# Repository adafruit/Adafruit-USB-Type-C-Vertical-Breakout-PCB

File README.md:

## Adafruit USB Type C Vertical Breakout - Downstream Connection PCB

<a href="http://www.adafruit.com/products/5993"><br/>
Click here to purchase one from the Adafruit shop</a>

PCB files for the Adafruit USB Type C Vertical Breakout - Downstream Connection. 

Format is EagleCAD schematic and board layout
* https://www.adafruit.com/product/5993

### Description

Throw out all those Mini and Micro B USB cables you have in a plastic bin; the next generation of USB connectors is here with USB C! You will start to see these connectors pop up on all sorts of devices as the industry moves from micro B or lightening to the new standard. Well, at least until the next standard comes out.

This is the vertical version. We also carry a classic 'horizontal' USB-C breakout here.

USB C features a symmetric/reversible connector, more data pins, and higher current output capability. But, for most developers, the pin usage you know and love from older USB will work just fine. This breakout gives you all the basics you need and a resistor configuration that mimics classic USB 2.0 for a downstream connection

The two 5.1K resistors on the CC pins indicate to the upstream port to provide 5V and up to 1.5A (whether the upstream can supply that much current depends on what you're connecting to.

For most usages, you can connect VBUS to your 5V input, GND to ground, and D+ and D- as you expect. You can monitor the CC and SBU pins to determine cable polarity or send side-band data. Or leave them disconnected.

Since this connector is vertical, we give you two identical breakout strips so it will stand flat on a breadboard, plus four mounting holes in case you want to attach this to an enclosure.

[For more details, we like this Introduction to USB C app note.](http://ww1.microchip.com/downloads/en/appnotes/00001953a.pdf)

### License

Adafruit invests time and resources providing this open source design, please support Adafruit and open-source hardware by purchasing products from [Adafruit](https://www.adafruit.com)!

Designed by Limor Fried/Ladyada for Adafruit Industries.

Creative Commons Attribution/Share-Alike, all text above must be included in any redistribution. 
See license.txt for additional details.

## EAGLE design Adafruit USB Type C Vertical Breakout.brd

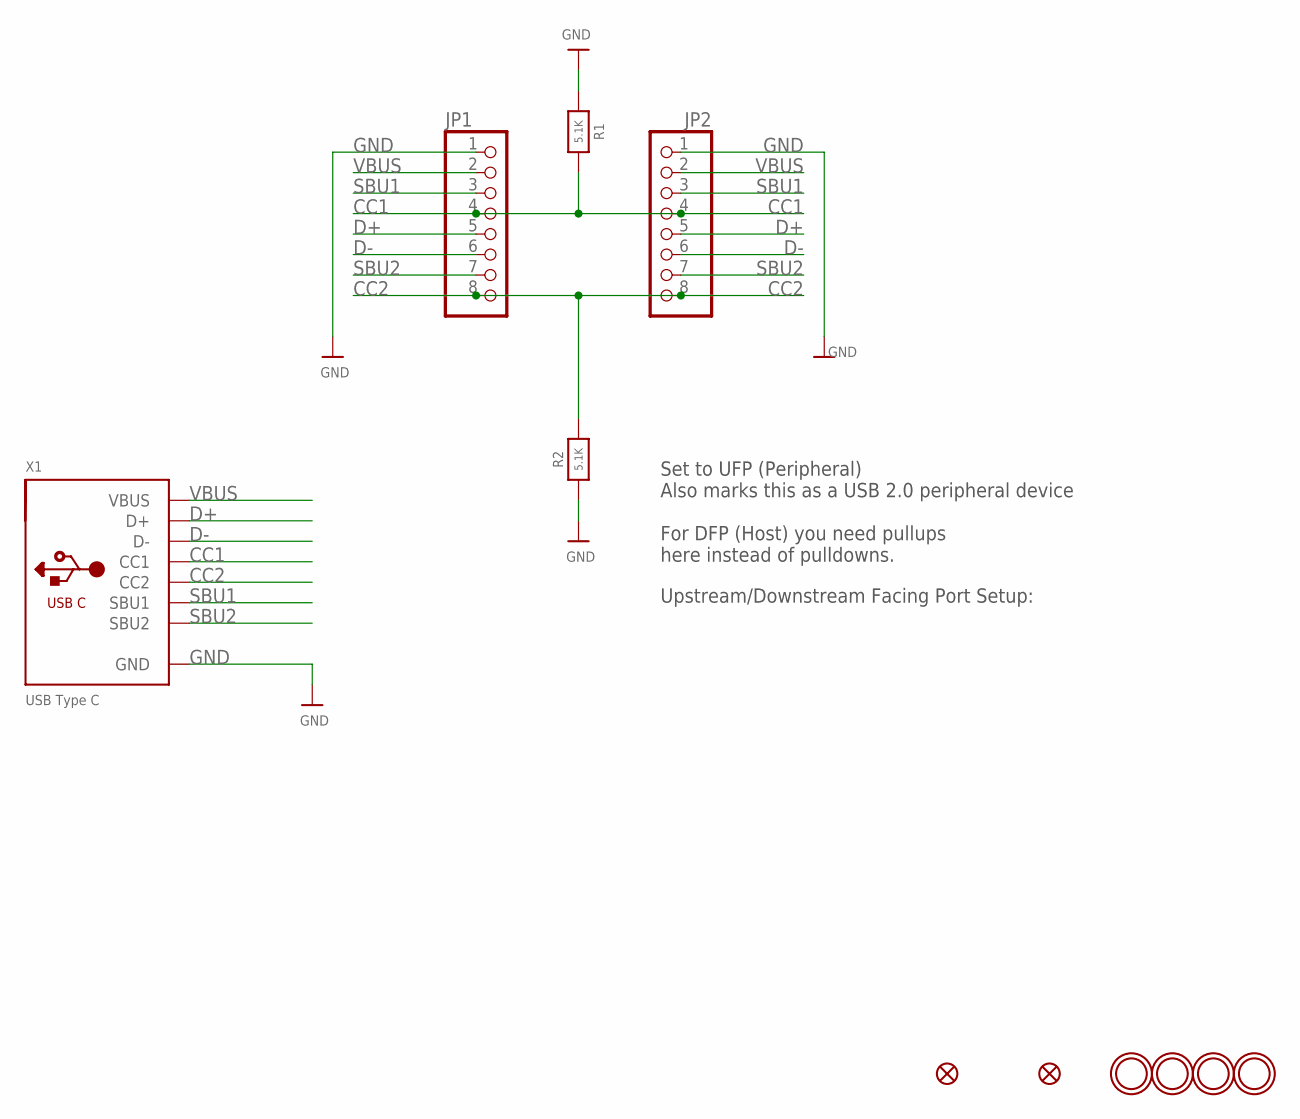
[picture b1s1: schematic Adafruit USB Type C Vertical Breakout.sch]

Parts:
FID1, FID2: FIDUCIAL_1MM
JP1, JP2: HEADER-1X876MIL; 1X08_ROUND_76
R1, R2: 5.1K; 0603-NO
U$1, U$2, U$10, U$11: MOUNTINGHOLE2.5; MOUNTINGHOLE_2.5_PLATED
X1: USB Type C; USB_C_VERTICAL

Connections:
CC1: JP1.4, JP2.4, R1.2, X1.A5 (CC1)
CC2: JP1.8, JP2.8, R2.2, X1.B5 (CC2)
D+: JP1.5, JP2.5, X1.A6 (D+), X1.B6 (D+)
D-: JP1.6, JP2.6, X1.A7 (D-), X1.B7 (D-)
GND: JP1.1, JP2.1, R1.1, R2.1, X1.A1 (GND), X1.A12 (GND), X1.B1 (GND), X1.B12 (GND), X1.P$1 (GND), X1.P$2 (GND), X1.P$3 (GND), X1.P$4 (GND)
SBU1: JP1.3, JP2.3, X1.A8 (SBU1)
SBU2: JP1.7, JP2.7, X1.B8 (SBU2)
VBUS: JP1.2, JP2.2, X1.A4 (VBUS), X1.A9 (VBUS), X1.B4 (VBUS), X1.B9 (VBUS)

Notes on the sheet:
Set to UFP (Peripheral) Also marks this as a USB 2.0 peripheral device For DFP (Host) you need pullups here instead of pulldowns.
Upstream/Downstream Facing Port Setup:

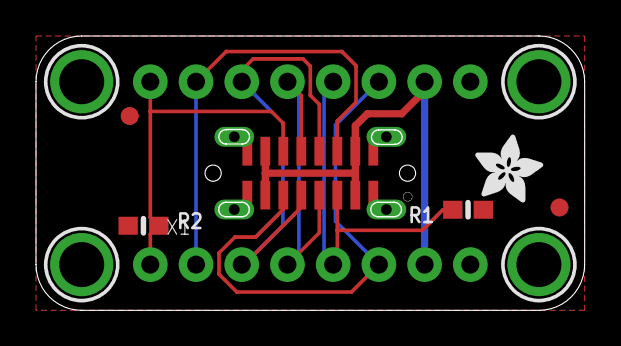
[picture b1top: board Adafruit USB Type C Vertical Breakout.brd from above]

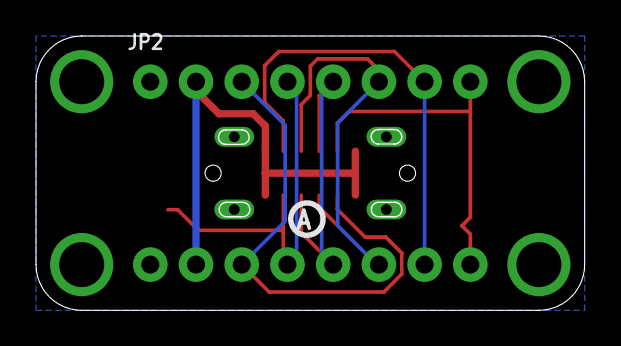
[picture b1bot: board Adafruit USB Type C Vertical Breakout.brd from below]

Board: 2 copper layers, 30.4 x 15.2 mm, 31 parts (3 on the bottom side), 8 nets.

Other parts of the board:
PLABEL0: PLABEL0
PLABEL1: PLABEL1
PLABEL2: PLABEL2
PLABEL3: PLABEL3
PLABEL4: PLABEL4
PLABEL5: PLABEL5
PLABEL6: PLABEL6
PLABEL7: PLABEL7
PLABEL8: PLABEL8
PLABEL9: PLABEL9
PLABEL10: PLABEL10
PLABEL11: PLABEL11
PLABEL12: PLABEL12
PLABEL13: PLABEL13
PLABEL14: PLABEL14
PLABEL15: PLABEL15
PLABEL16: PLABEL16
PLABEL17: PLABEL17
U$8: PCBFEAT-REV-040
U$12: ADAFRUIT_3.5MM

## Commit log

2024-07-08 cookiecutter

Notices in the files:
parts and their libraries:
microbuilder: This work is placed in the public domain, and may be freely used for commercial and non-commercial work with the following conditions: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
